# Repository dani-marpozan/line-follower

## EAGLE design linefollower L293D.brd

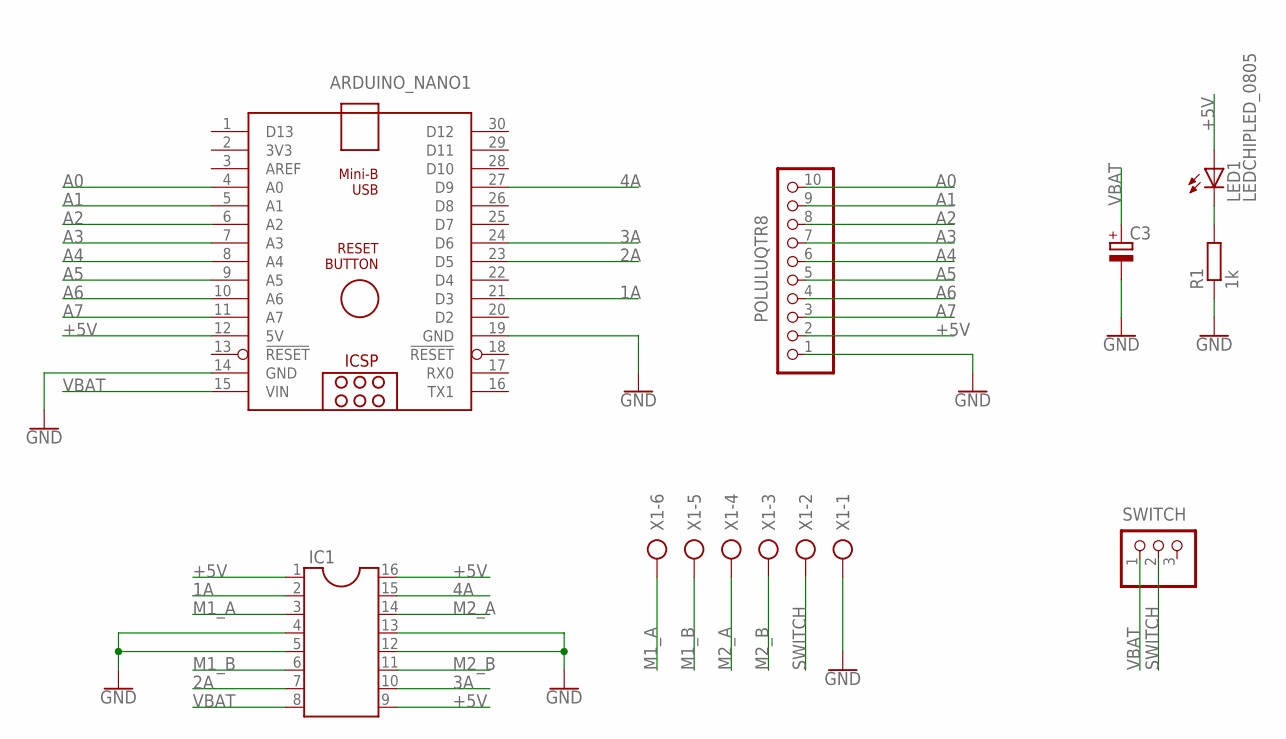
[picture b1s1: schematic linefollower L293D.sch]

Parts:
ARDUINO_NANO1: ARDUINO_NANO
C3: UCD1V221MNL1GS; CAPAE830X1050
IC1: DIL16
LED1: LEDCHIPLED_0805; CHIPLED_0805
POLULUQTR8: PINHD-1X10; 1X10
R1: 1k; R0805
SWITCH: PINHD-1X3; 1X03
X1: AK500/6

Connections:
1A: ARDUINO_NANO1.21 (D3), IC1.2
2A: ARDUINO_NANO1.23 (D5), IC1.7
3A: ARDUINO_NANO1.24 (D6), IC1.10
4A: ARDUINO_NANO1.27 (D9), IC1.15
+5V: ARDUINO_NANO1.12 (5V), IC1.1, IC1.9, IC1.16, LED1.A, POLULUQTR8.2
A0: ARDUINO_NANO1.4 (A0), POLULUQTR8.10
A1: ARDUINO_NANO1.5 (A1), POLULUQTR8.9
A2: ARDUINO_NANO1.6 (A2), POLULUQTR8.8
A3: ARDUINO_NANO1.7 (A3), POLULUQTR8.7
A4: ARDUINO_NANO1.8 (A4), POLULUQTR8.6
A5: ARDUINO_NANO1.9 (A5), POLULUQTR8.5
A6: ARDUINO_NANO1.10 (A6), POLULUQTR8.4
A7: ARDUINO_NANO1.11 (A7), POLULUQTR8.3
GND: ARDUINO_NANO1.14 (GND), ARDUINO_NANO1.19 (GND), C3.2 (-), IC1.4, IC1.5, IC1.12, IC1.13, POLULUQTR8.1, R1.1, X1.1
M1_A: IC1.3, X1.6
M1_B: IC1.6, X1.5
M2_A: IC1.14, X1.4
M2_B: IC1.11, X1.3
unnamed: LED1.C, R1.2
SWITCH: SWITCH.2, X1.2
VBAT: ARDUINO_NANO1.15 (VIN), C3.1 (+), IC1.8, SWITCH.1

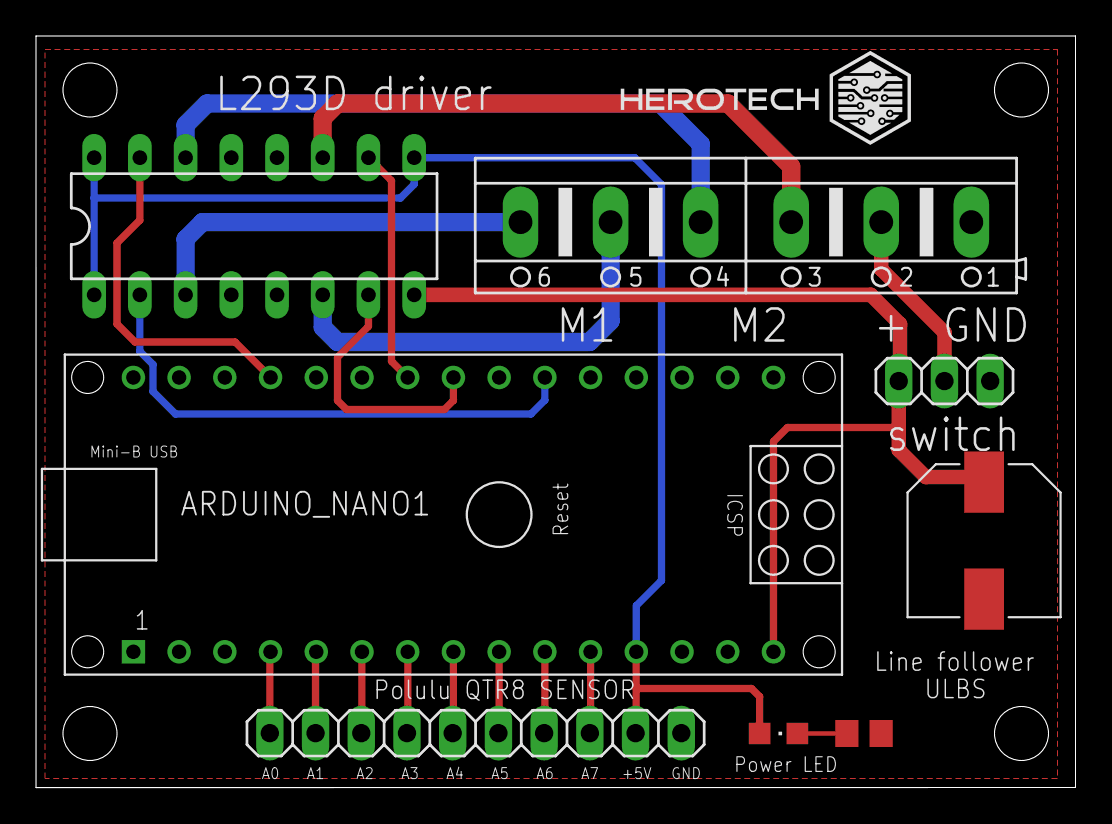
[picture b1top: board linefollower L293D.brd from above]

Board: 2 copper layers, 57.8 x 41.8 mm, 8 parts (0 on the bottom side), 21 nets.

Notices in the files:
parts and their libraries:
SparkFun-PowerSymbols: Licensing: Creative Commons ShareAlike 4.0 International - https://creativecommons.org/licenses/by-sa/4.0
